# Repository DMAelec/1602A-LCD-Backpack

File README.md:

# 1602A LCD Backpack

## Introduction
The 1602A LCD Serial Backpack is a ATMEGA328 microcontroller module that mounts behind standard 16 character x 2 column LCD displays.
It is essentially an Arduino Uno with a built in LCD and RS-232 serial port. The boards are designed using SMD parts reducing component
size, making it fit neatly behind the display.

A board with 4 tactile buttons for user input is included in this repo.

#### LCD Running

#### LCD Backpack and 4 Button Board

## Features

* 1602A_LCD Serial Backpack
  * PWM backlight
  * On board speaker
  * Analog voltage monitor
  * RS232 serial interface with auto reset

* BTNPAD_TYPE_B
  * 4 button board with pullup resistors
  * LED backlit buttons
  
All features are optional and can be left unpopulated as the signals are brought out to a pin header

## Hardware Documentation

### Schematics

[1602A IDE IO pinout (bmp)](/Pics/1602_IO_pinout(IDE).bmp)

[1602A_LCD Serial Schematic (pdf)](/1602A_LCD%20Serial%20Backpack/1602A_LCD%20Serial%20Backpack-SCHEMATIC.pdf)

[BTNPAD_TYPE_B Schematic (pdf)](/BTNPAD_TYPE_B/BTNPAD_TYPE_B-SCHEMATIC.pdf)

### Jumpers, Switches and Pots

#### JP1 - PWM Backlight Select
|  Position  |            Description               |
|------------|--------------------------------------|
| 1-2 closed | Use LCD PWM Backlight (D10)          |
| 2-3 closed | Continuous Backlight (Unpopulate Q1) |

#### JP2 - Enable Auto Reset
|  Position  |            Description               |
|------------|--------------------------------------|
| closed     | Auto Reset on DTR                    |
| open       | Auto Reset Disabled                  |

#### SW1 - Reset Switch
Press SW1 to reset the MCU

#### RV1 - LCD Contrast 
Adjust RV1 to set the LCD contrast

### Parts List
Most parts are SMD and can be ordered from Mouser or Digikey

#### 1602A_LCD Serial Backpack - REV2
| Component Type     | Reference             | Description                                      |
|--------------------|-----------------------|--------------------------------------------------|
| Resistor           | R1                    | 10K Ohm, 0805 SMD                                |
| Resistor           | R2                    | 100K Ohm, 1206 SMD                               |
| Resistor           | R3                    | 10K Ohm, 1206 SMD                                |
| Resistor           | R4                    | 330 Ohm, 1206 SMD                                |
| Resistor           | R5, R7, R8, R9        | 1K Ohm, 0805 SMD                                 |
| Resistor           | R6                    | 6.8K Ohm, 0805 SMD                               |
| Trim Pot           | RV1                   | 10K Ohm, 3362P THT                               |
| Capacitor          | C1, C3, C6, C11, C12  | 0.1uF, 25V, MLCC, 0805 SMD                       |
| Capacitor          | C2                    | 22uF, 10V, Tant, Kemet Case B (1311) SMD         |
| Capacitor          | C4, C5                | 22pF, 25V, MLCC, 0805 SMD                        |
| Capacitor          | C7                    | 0.047uF, 25V, MLCC, 0805 SMD                     |
| Capacitor          | C8, C9, C10           | 0.33uF, 25V, MLCC, 0805 SMD                      |
| Transistor         | Q1, Q2                | MMBT3904, SOT-23 SMD                             |
| Diode              | D1                    | 1N4001 (M1), DO-214AC SMD                        |
| Diode              | D2                    | 1N4148, Mini MELF SMD                            |
| LED                | D3                    | Green LED, 0805 SMD                              |
| Integrated Circuit | U1                    | LM1117-5.0 LDO Regulator, TO252-3 (DPAK) SMD     |
| Integrated Circuit | U2                    | ATMEGA328P-AU 8-Bit Microcontroller, TQFP-32 SMD |
| Integrated Circuit | U3                    | MAX3232 RS-232 Interface, SOIC-16-N SMD          |
| LCD Display        | DS1                   | 1602A LCD Character Display, THT                 |
| Speaker            | SPKR1                 | CST-951RP Piezo Speaker, THT                     |
| Crystal            | Y1                    | 16MHz, 8pF, 2.5mm x 2.0mm SMD                    |
| Tactile Switch     | SW1                   | PTS636-SM25 Tactile Switch, SMD                  |
| Terminal Block     | J1                    | 2 Pos Screw Terminal Block, 5.08mm pitch THT     |
| Pin Header         | J2                    | 2x12 Pin Header, 2.54mm pitch THT                |
| JST Connector      | J3                    | S4B-PH-K JST Connector, 2.0mm pitch THT          |
| PCB                |                       | 1602A_LCD Serial Backpack (REV2), 2 Layer PCB    |
| Misc               |                       | LCD Mounting Hardware                            |

#### BTNPAD_TYPE_B - REV1
| Component Type     | Reference             | Description                                      |
|--------------------|-----------------------|--------------------------------------------------|
| Resistor           | R1, R2, R3, R4, R5    | 10K Ohm, 0805 SMD                                |
| Resistor           | R6                    | 1K Ohm, 0805 SMD                                 |
| Resistor           | R7, R8                | 56 Ohm, 1206 SMD                                 |
| Transistor         | Q1                    | MMBT3904, SOT-23 SMD                             |
| LED                | D1, D2, D3, D4        | Green LED, 0805 SMD                              |
| Tactile Switch     | SW1, SW2, SW3, SW4    | PTS526-SK08 Tactile Switch, SMD                  |
| Pin Header         | J1                    | 1x7 Pin Header, 2.54mm pitch THT                 |
| PCB                |                       | BTNPAD_TYPE_B (REV1), 2 Layer PCB, White S-Mask  |

## Firmware Documentation

### Arduino IDE LCD Code
The backpack is compatible with the standard Arduino Liquid Crystal library but some modification to the code is required

In the main code, change the Arduino pin number line to:
const int rs = 7, en = 6, d4 = 5, d5 = 4, d6 = 3, d7 = 2;

For PWM backlight functionality, add line: 
analogWrite(10, 255);

## Release Notes

### Known Issues

* 1602A_LCD Serial Backpack - REV2
  * Auto reset feature is erratic and may cause latchup
    * Workaround: bodge a 1N4148 diode between +5V and Reset or don't use
  * Analog voltage monitoring is after the DC IN protection diode, readings may be inaccurate
    * Workaround: adjust code to account for diode voltage drop

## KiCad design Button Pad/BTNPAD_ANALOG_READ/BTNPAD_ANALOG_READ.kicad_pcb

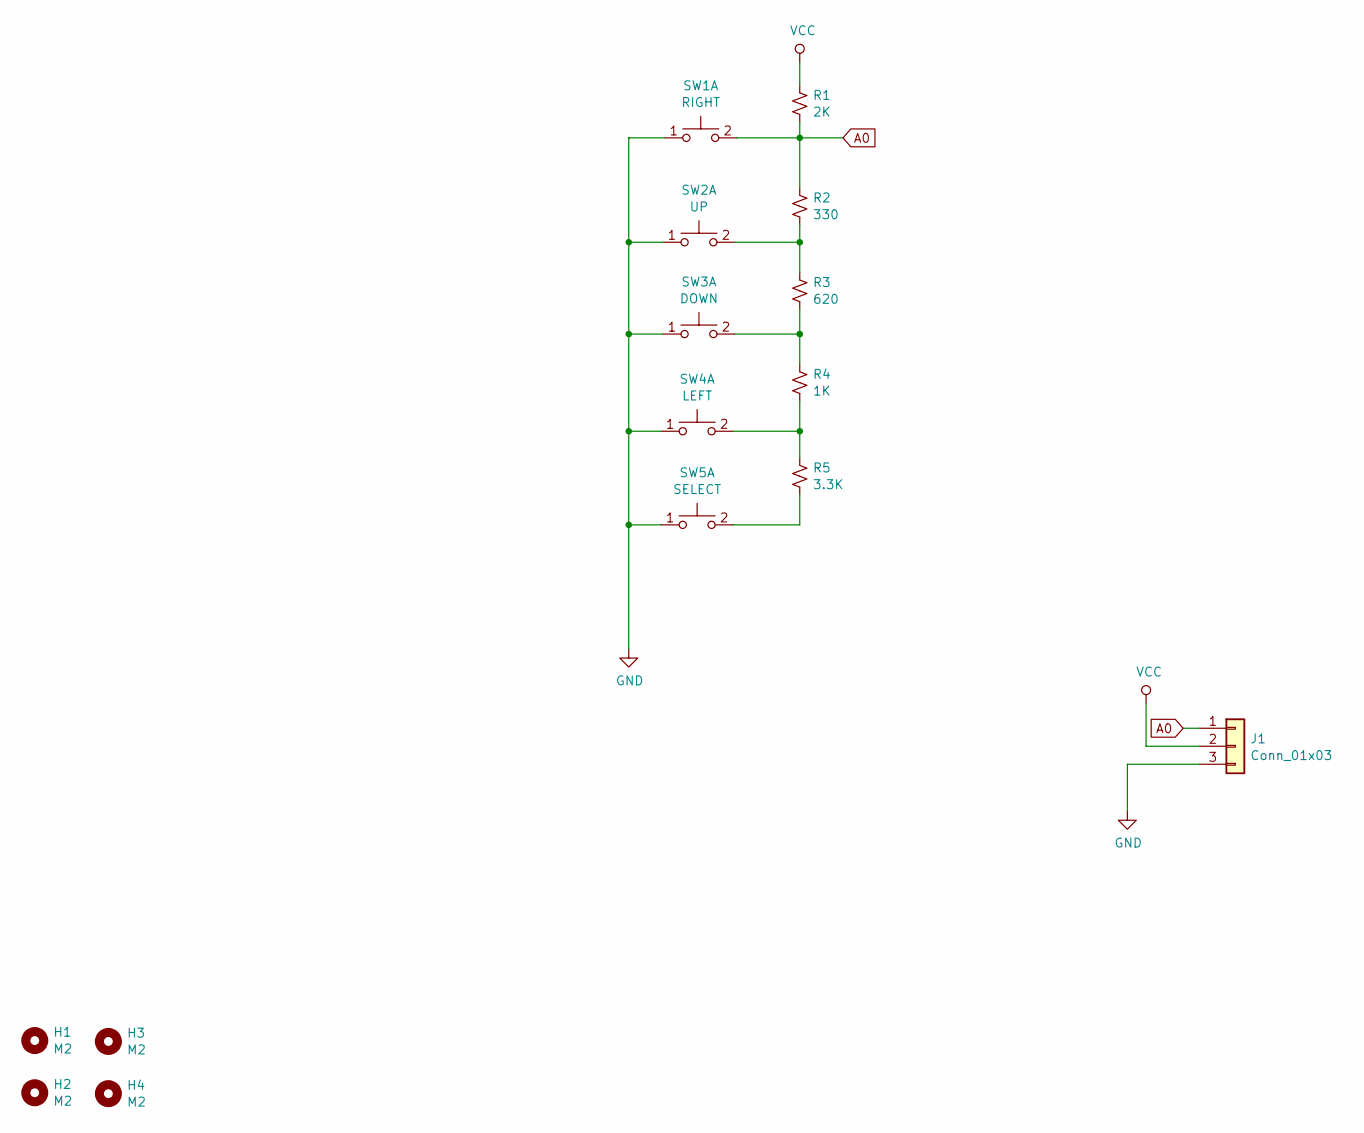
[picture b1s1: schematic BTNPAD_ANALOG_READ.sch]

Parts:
H1, H2, H3, H4: M2; MountingHole_2.5mm
J1: Conn_01x03; PinHeader_1x03_P2.54mm_Vertical
R1: 2K; R_0805_2012Metric_Pad1.15x1.40mm_HandSolder
R2: 330; R_0805_2012Metric_Pad1.15x1.40mm_HandSolder
R3: 620; R_0805_2012Metric_Pad1.15x1.40mm_HandSolder
R4: 1K; R_0805_2012Metric_Pad1.15x1.40mm_HandSolder
R5: 3.3K; R_0805_2012Metric_Pad1.15x1.40mm_HandSolder
SW1: RIGHT; SW_SPST_CK_RS282G05A3
SW2: UP; SW_SPST_CK_RS282G05A3
SW3: DOWN; SW_SPST_CK_RS282G05A3
SW4: LEFT; SW_SPST_CK_RS282G05A3
SW5: SELECT; SW_SPST_CK_RS282G05A3

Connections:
A0: J1.1, R1.2, R2.1, SW1.2 (D)
GND: J1.3, SW1.1 (C), SW2.1 (C), SW3.1 (C), SW4.1 (C), SW5.1 (C)
unnamed: R2.2, R3.1, SW2.2 (D)
unnamed: R3.2, R4.1, SW3.2 (D)
unnamed: R4.2, R5.1, SW4.2 (D)
unnamed: R5.2, SW5.2 (D)
VCC: J1.2, R1.1

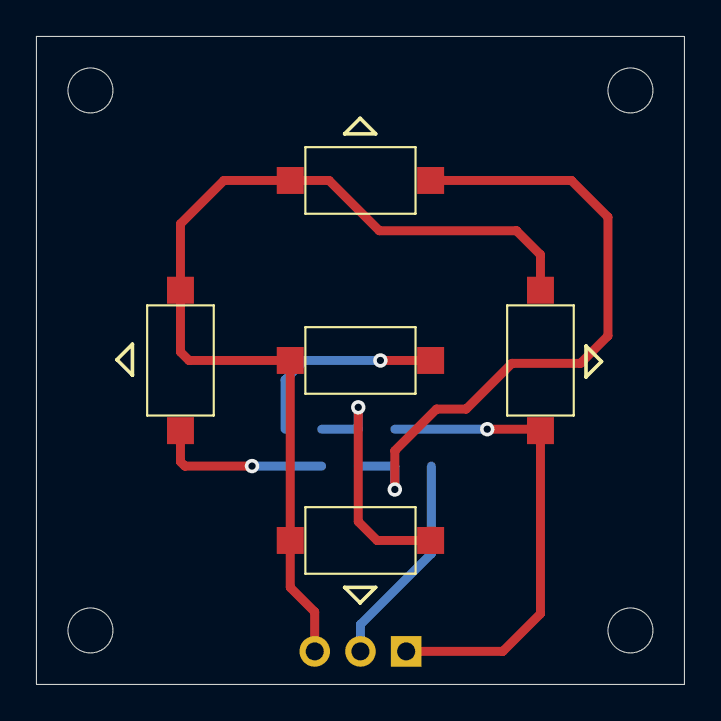
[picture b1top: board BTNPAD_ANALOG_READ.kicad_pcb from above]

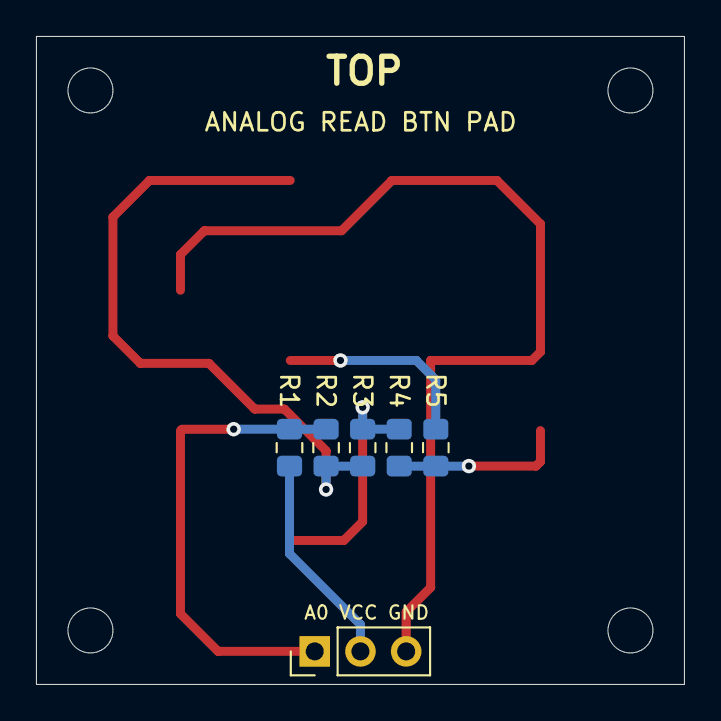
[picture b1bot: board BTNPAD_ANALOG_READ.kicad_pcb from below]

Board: 2 copper layers, 36.0 x 36.0 mm, 15 parts (6 on the bottom side), 7 nets.

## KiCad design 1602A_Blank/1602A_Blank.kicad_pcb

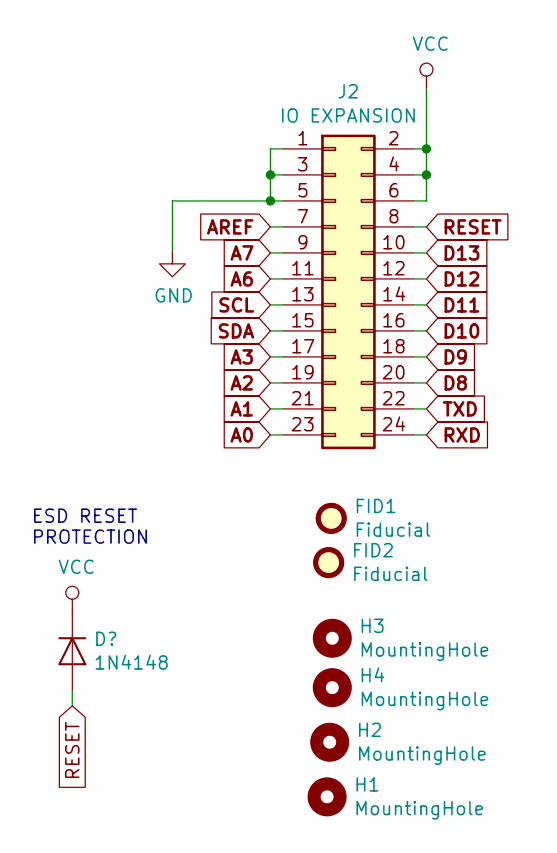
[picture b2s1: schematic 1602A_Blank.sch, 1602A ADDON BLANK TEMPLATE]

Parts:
FID1, FID2: Fiducial; Fiducial_1mm_Mask2mm
H1, H2, H3, H4: MountingHole; MountingHole_2.5mm_Pad
J2: IO EXPANSION; PinSocket_2x12_P2.54mm_Vertical

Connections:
A0: J2.23
A1: J2.21
A2: J2.19
A3: J2.17
A6: J2.11
A7: J2.9
AREF: J2.7
D8: J2.20
D9: J2.18
D10: J2.16
D11: J2.14
D12: J2.12
D13: J2.10
GND: J2.1, J2.3, J2.5
RESET: J2.8
RXD: J2.22
SCL: J2.13
SDA: J2.15
TXD: J2.24
VCC: J2.2, J2.4, J2.6

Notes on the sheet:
ESD RESET PROTECTION

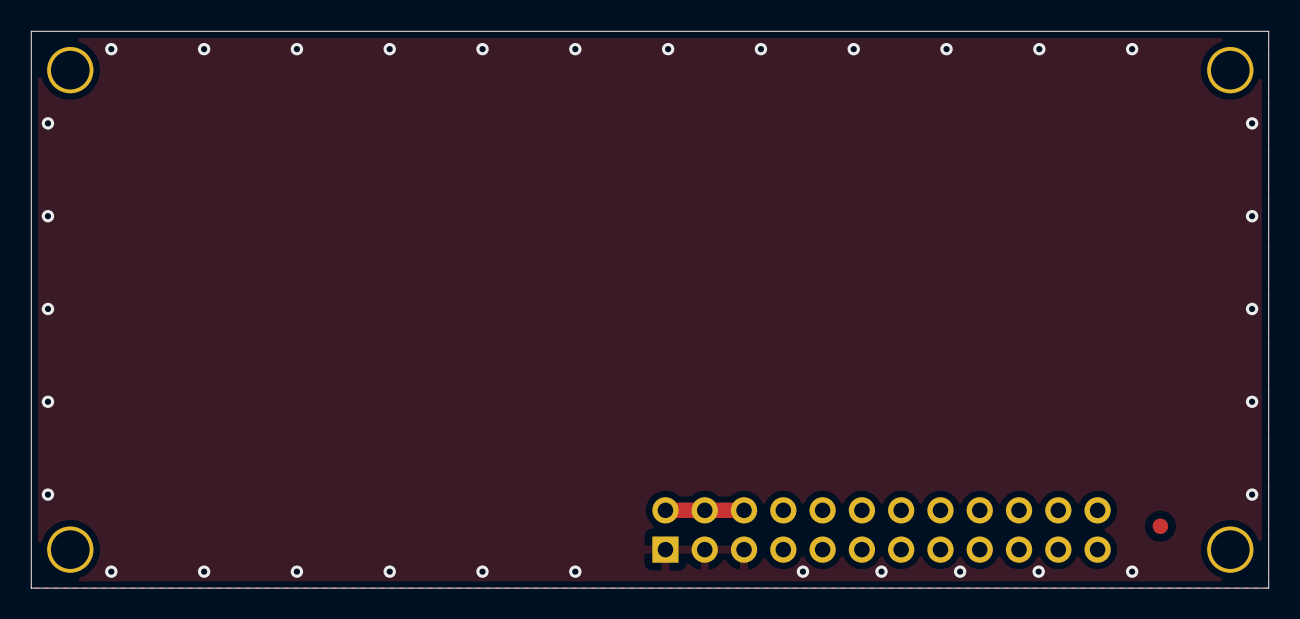
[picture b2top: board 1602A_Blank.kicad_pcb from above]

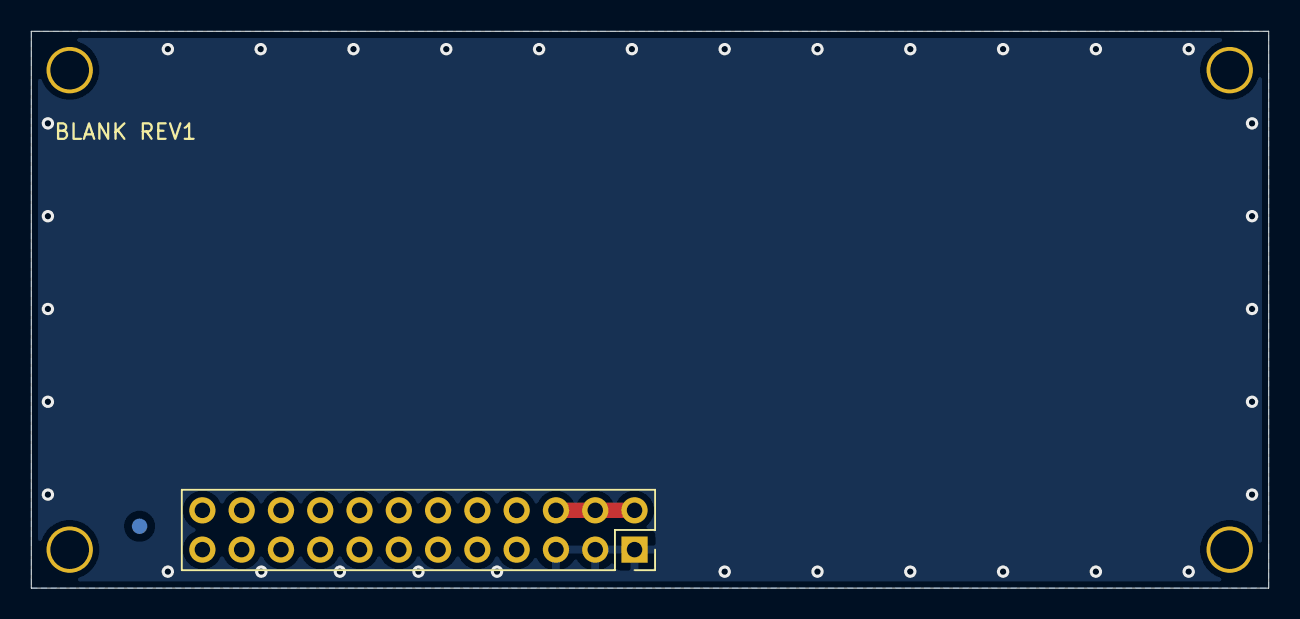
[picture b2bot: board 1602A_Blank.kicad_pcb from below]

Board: 2 copper layers, 80.0 x 36.0 mm, 7 parts (2 on the bottom side), 2 nets.

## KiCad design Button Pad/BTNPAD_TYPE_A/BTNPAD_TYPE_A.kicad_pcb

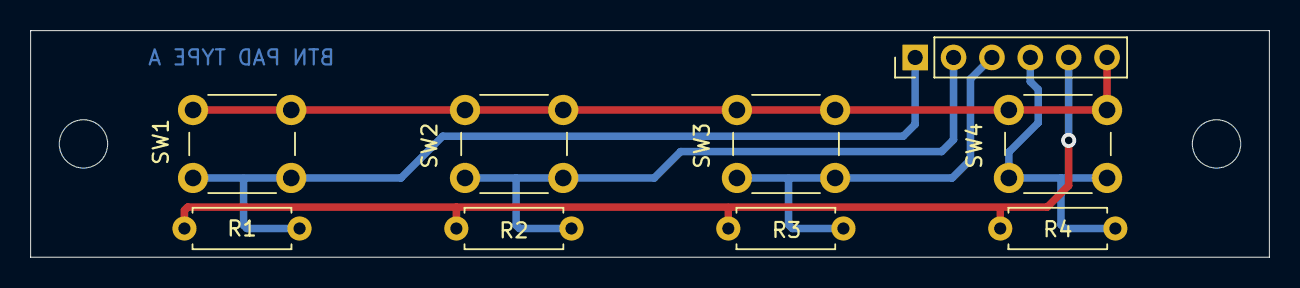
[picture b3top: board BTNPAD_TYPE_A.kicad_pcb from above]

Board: 2 copper layers, 82.0 x 15.0 mm, 11 parts (0 on the bottom side), 6 nets.

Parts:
H1, H2: M3; MountingHole_3.2mm_M3
J1: Conn_01x06; PinHeader_1x06_P2.54mm_Vertical
R1, R2, R3, R4: 10K; R_Axial_DIN0207_L6.3mm_D2.5mm_P7.62mm_Horizontal
SW1, SW2, SW3, SW4: SPST; SW_PUSH_6mm

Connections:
B1: J1.1, R1.2, SW1.2
B2: J1.2, R2.2, SW2.2
B3: J1.3, R3.2, SW3.2
B4: J1.4, R4.2, SW4.2
GND: J1.6, SW1.1, SW2.1, SW3.1, SW4.1
VCC: J1.5, R1.1, R2.1, R3.1, R4.1

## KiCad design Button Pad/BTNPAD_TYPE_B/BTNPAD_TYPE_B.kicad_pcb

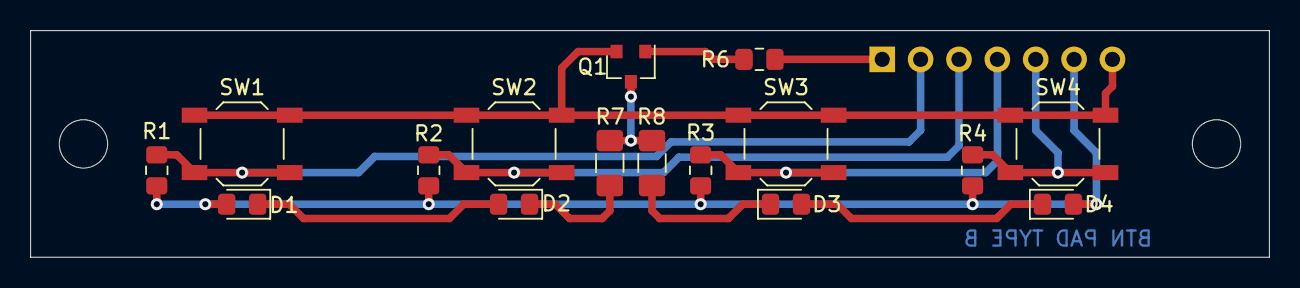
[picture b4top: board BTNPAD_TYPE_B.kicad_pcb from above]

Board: 2 copper layers, 82.0 x 15.0 mm, 19 parts (1 on the bottom side), 13 nets.

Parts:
D1, D2, D3, D4: LED; LED_0805_2012Metric_Pad1.15x1.40mm_HandSolder
H1, H2: M3; MountingHole_3.2mm_M3
J1: IO; PinHeader_1x07_P2.54mm_Vertical
Q1: MMBT3904; SOT-23
R1, R2, R3, R4, R6: 10K; R_0805_2012Metric_Pad1.15x1.40mm_HandSolder
R7, R8: 36; R_1206_3216Metric_Pad1.42x1.75mm_HandSolder
SW1, SW2, SW3, SW4: SPST; SW_SPST_TL3342

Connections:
B1: J1.2, R1.2, SW1.2
B2: J1.3, R2.2, SW2.2
B3: J1.4, R3.2, SW3.2
B4: J1.5, R4.2, SW4.2
GND: J1.7, Q1.2, SW1.1, SW2.1, SW3.1, SW4.1
LED: J1.1, R6.1
unnamed: D1.1, D2.2
unnamed: D2.1, R7.1
unnamed: D3.1, R8.1
unnamed: D3.2, D4.1
unnamed: Q1.1, R6.2
unnamed: Q1.3, R7.2, R8.2
VCC: D1.2, D4.2, J1.6, R1.1, R2.1, R3.1, R4.1
